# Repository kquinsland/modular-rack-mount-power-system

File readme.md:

# Modular Rack Power

This is a "side-quest" project on the way to building a small "mini rack" dedicated to hosting GH/A runners.

I'll do the CAD and standalone development here before integrating it into the larger project.
The goal is to have a modular system of a backplane and multiple carrier modules that can be swapped in and out to provide different power configurations as needed.
As long as the power supply can handle it, backplanes may share/daisy-chain the
input distribution needed by their carrier modules.

Hardware, firmware, and host tooling for a modular mini-rack power system.

## Boards

- `backplane`: STM32C092/CAN-FD backplane with six carrier slots, power
  distribution, aggregate current monitoring, fan control, and a status
  NeoPixel.
- `carrier`: Mates with one backplane slot and hosts an SW3538 USB-C PD module.

Every backplane and carrier is an independent STM32C092 CAN-FD node. There is no
I2C mux and no controller/proxy relationship between nodes. Earlier hardware and
firmware were research prototypes and are not compatibility targets.

## Layout

```text
firmware/
  Cargo.toml
  backplane/
  carrier/
  bootloader/
  crates/
  tools/
  xtask/
  docs/pdcan/
hardware/
  boards/
    backplane/
    carrier/
  libraries/
    symbols/
    footprints/
    3dmodels/
  mechanical/
docs/
scripts/
build/
releases/
```

`build/` is for generated local outputs. `releases/` is for fabrication packages that should be preserved exactly as sent to a board house.

See [`firmware/README.md`](firmware/README.md) for workspace commands and the
current hardware/firmware contract. Run `mise run firmware:check` from this
directory, or run Cargo commands from `firmware/`. The reviewed implementation
plan is kept in [`firmware/plan.md`](firmware/plan.md).

## Documentation site

The public-facing project documentation is maintained in [`site/`](site/) and
is intended for <https://mrps.karlquinsland.com/>. Run `mise run site:serve` for
local preview or `mise run site:build` for a production build. Create journal
entries with `mise run worklog:new -- "Concise Summary"` to create
`site/content/worklogs/YYYY/MM/DD - Concise Summary/index.md` with matching
front matter and an adjacent `_files/` directory for page resources.

## Misc

I can't believe that it's STILL such a pain in the ass to use LCSC to search for parts that are stocked by the SMT service.
https://yaqwsx.github.io/jlcparts/#/

Also super useful reference: https://www.tinkervault.com/usb-power-sources/dc-pd30-adapters
It's how I 'caught' that the `sw3538` based module I am using is non-standard 140W, later confirmed:

- https://en.eeworld.com.cn/Reference_Designs/detail/81702
- https://github.com/happyme531/h1_SW35xx/issues/13#issuecomment-4361605621

https://github.com/Shrike-Lab/HomeLab-PDU-V1/blob/main/ASSEMBLY/README.md#pcb-tray

Plan was to use APK43070 but they do not support MCU controlling it via i2c

https://meron33.hatenablog.com/entry/2026/02/07/112759

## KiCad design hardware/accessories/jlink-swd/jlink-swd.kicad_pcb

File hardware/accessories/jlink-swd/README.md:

# J-Link SWD adapter

This standalone 51.2 × 42 mm, two-layer board plugs directly into the SEGGER 20-pin ARM debug port. The keyed six-pin cable reaches backplane J10 or carrier J2. Both targets use the same contact assignments.

| Ref | Fit | Assembly |
| --- | --- | --- |
| J1 | Sullins SFH11-PBPC-D10-RA-BK ([LCSC C3319874](https://www.lcsc.com/product-detail/C3319874.html)) | Polarized 2×10 right-angle **female** socket, component side. Its mouth projects 7.74 mm past the PCB edge. |
| J2 | Leave empty | Central 2×10 through-hole tap. Every position connects to the same numbered position on J1. |
| J3 | 2×3 keyed vertical IDC **male** box header, 2.54 mm | Match the shroud opening to the footprint outline. Plug the TC2030-IDC-NL ribbon socket in here. |
| J4 | 2×2 straight male pin header, 2.54 mm | Pins 1 and 3 tap J-Link pin 19 (5 V where supported). Pins 2 and 4 are GND. |
| J5 | External 3.3 V input, 1×2 | Pin 1 is regulated 3.3 V, pin 2 is GND. |
| J6 | Source selector, 1×3 | Fit one shunt. Pins 1–2 select J-Link pin 1 (VTref), pins 2–3 select J5. |
| J7 | Target-current link, 1×2 | Pin 1 is the selected source, pin 2 is the target rail. Fit a shunt for normal adapter-powered operation. |
| J10 | Clone 3.3 V auxiliary tap, 2×2 | Pins 1 and 3 tap J-Link pin 2. Pins 2 and 4 are GND. |
| H1–H4 | 3.0 mm plated GND holes with 6.0 mm exposed pads | Hole centers form a 40.8 × 35.0 mm rectangle. Each pad connects to the top and bottom GND pours. Conductive mounting hardware touching a pad shares the target and J-Link ground. |

## Probe connections

| J3 / target pad | Signal | J1 / J2 |
| ---: | --- | --- |
| 1 | Target 3V3 | 1 through J6 (1–2) and J7 |
| 2 | SWDIO | 7 |
| 3 | Active-low reset | 15 |
| 4 | SWCLK | 9 |
| 5 | GND | 4, 6, 8, 10, 12 |
| 6 | Open | — |

## Power and current profiling

Change shunts with the probe and target unpowered. J4 and J10 each provide two power/GND pairs for leads. A shunt across either pair would short the supply. The odd-numbered column carries power and the even-numbered column is ground. Pin 1 has a square pad.

| Mode | J6 | J7 | Connection |
| --- | --- | --- | --- |
| Self-powered target with standard VTref sensing | 1–2 | Fit | Target 3.3 V reaches the probe’s pin 1 so it can sense the target logic level. |
| Probe with a verified supply on **pin 1** | 1–2 | Fit | Pin 1 can feed an otherwise unpowered target only when that probe explicitly supports it. |
| External regulated 3.3 V | 2–3 | Fit | Connect supply positive to J5.1 and return to J5.2. Probe pin 1 is isolated. |
| Measure current supplied by the adapter | Select the active supply | Replace shunt with ammeter | Meter positive to J7.1 (source), return to J7.2 (target). |

SEGGER specifies pin 1 as a target-voltage reference input. Selecting VTref with a standard probe and an unpowered target supplies no power. Conversely, external mode disconnects the probe’s VTref input, so a debugger that requires target-voltage sensing may refuse to attach in that mode. To debug an independently powered target using standard voltage sensing, use the first row.

The clone’s pin-2 output is available at J10 independently of J6. Verify the voltage and current capability of the particular probe before drawing power. To use that output as the target supply, patch J10.1 or J10.3 to J5.1, select EXT and fit J7. For a profiler with its own supply, feed J5 directly from the profiler. When the adapter powers the target, disconnect its normal power input. Grounds remain common throughout.

Reserved J-Link contacts 14, 16, 18, and 20 each have their own tap.

J2’s front silkscreen follows the SEGGER pin numbers. Odd positions are on the left and even positions on the right when the text is upright. R denotes a reserved position. P2 marks the optional clone supply and NC marks pin 17.

## Mating orientation

With J1's polarization bump up, looking into the **female mating face**, the upper row runs from SEGGER pin 1 at the left to pin 19 at the right. The lower row runs from pin 2 to pin 20. The upper contacts bend to the through-hole row farther from the board edge. The square J1 pad is VTref. Before powering a first assembly, verify continuity from that socket contact through J6 (1–2) and the fitted J7 link to J3 pin 1 and from the opposite end of the same row to both J4 pins 1 and 3.

See the [SEGGER 20-pin connector drawing](https://kb.segger.com/20-pin_J-Link_Connector), the [Sullins SFH11 mechanical drawing](https://sullinscorp.com/catalogs/147_PAGE119_.100_SFH11_SERIES_FEMALE_HDR_ST_RA.pdf), and the [TC2030-IDC-NL cable pin map, sheet 2](https://www.tag-connect.com/wp-content/uploads/bsk-pdf-manager/2019/12/TC2030-IDC-NL-Datasheet-Rev-B.pdf#page=2).

The project includes a [mechanical STEP model of J1](models/SFH11-PBPC-D10-RA-BK.step) with a keyed housing, mating openings, and 20 solder tails. It was drawn from the Sullins dimensions and the assembly outline for this part in the [TI reference design](https://www.ti.com/lit/zip/SWRC397). Internal spring contacts are omitted.

## Production export

The front silkscreen identifies revision 1.1. The KiCad editor displays `YY-MM-DD` and `UNRELEASED` as working-copy placeholders, as on the main boards. After committing the layout being fabricated, generate the fabrication files and purchasing BOM with KiCad 10 and the JLCPCB Fabrication Toolkit installed:

```sh
mise run production:jlink-swd
```

The default output directory is `hardware/accessories/jlink-swd/production/YY.MM.DD-<hash>/`. The directory name and silkscreen both use the commit’s UTC date and first 12 hex digits. To choose a different destination, run `mise run production:jlink-swd /path/to/output`.

Select bare-board fabrication and upload only `jlink-swd.zip`. All connector pads and drills are included for hand soldering. The separate `positions.csv` contains its column headings and zero placement rows. The export also writes the footprint inventory (`designators.csv`) and electrical-test netlist (`netlist.ipc`).

Use `bom.csv` for the hand-assembled components. Leave J2 empty and obtain two removable 2.54 mm jumper shunts for J6 and J7.

The task uses `/usr/bin/python3` by default. Set `KICAD_PYTHON` to another interpreter with the KiCad and wxPython bindings if needed.

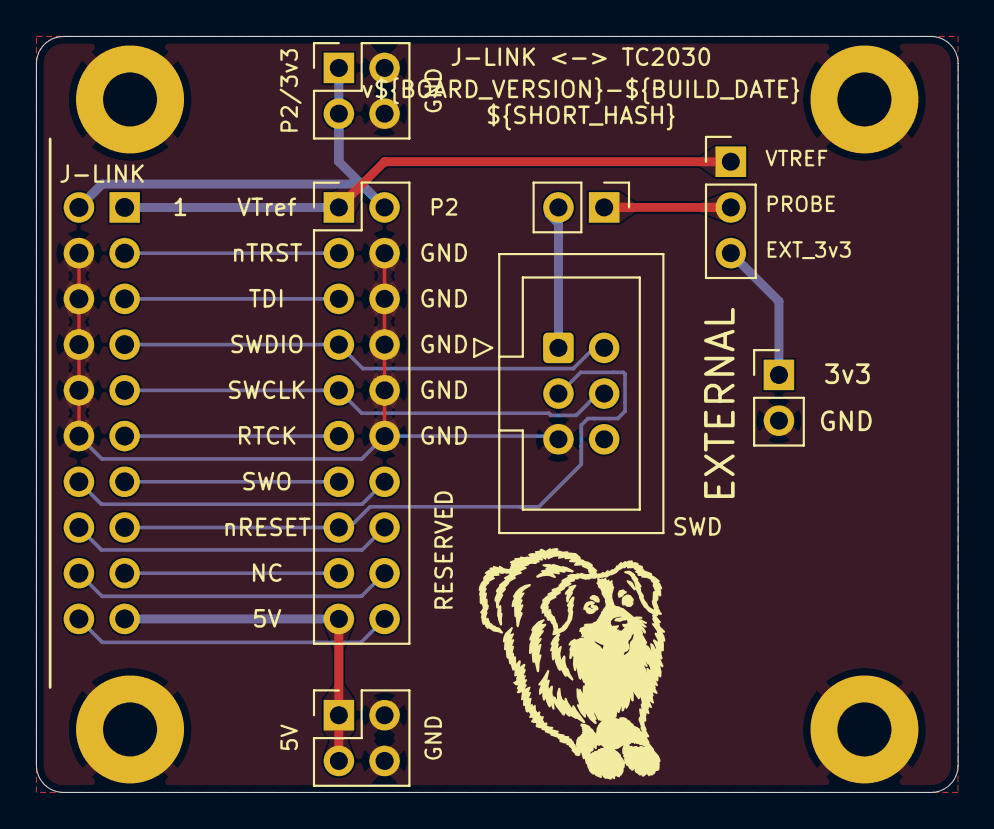
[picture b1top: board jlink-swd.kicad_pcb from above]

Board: 2 copper layers, 51.2 x 42.0 mm, 12 parts (0 on the bottom side), 19 nets.

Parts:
H1, H2, H3, H4: 3.0 mm; MountingHole_3mm_Pad
J1: SFH11-PBPC-D10-RA-BK
J2: 20-pin tap (DNP); PinHeader_2x10_P2.54mm_Vertical
J3: TC2030-IDC-NL; IDC-Header_2x03_P2.54mm_Vertical
J4: 5V / GND taps; PinHeader_2x02_P2.54mm_Vertical
J5: External 3.3V; PinHeader_1x02_P2.54mm_Vertical
J6: 3.3V source; PinHeader_1x03_P2.54mm_Vertical
J7: Target current; PinHeader_1x02_P2.54mm_Vertical
J10: Clone 3V3 / GND taps; PinHeader_2x02_P2.54mm_Vertical

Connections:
+3V3: J3.1, J7.2
+5V: J1.19, J2.19, J4.1, J4.3
/EXT_3V3: J5.1, J6.3
/P2: J1.2, J2.2, J10.1, J10.3
/P17: J1.17, J2.17
/PROBE_VTREF: J1.1, J2.1, J6.1
/RES14: J1.14, J2.14
/RES16: J1.16, J2.16
/RES18: J1.18, J2.18
/RES20: J1.20, J2.20
/RTCK: J1.11, J2.11
/SELECTED_3V3: J6.2, J7.1
/SWCLK: J1.9, J2.9, J3.4
/SWDIO: J1.7, J2.7, J3.2
/SWO: J1.13, J2.13
/TDI: J1.5, J2.5
/nRESET: J1.15, J2.15, J3.3
/nTRST: J1.3, J2.3
GND: H1.1, H2.1, H3.1, H4.1, J1.4, J1.6, J1.8, J1.10, J1.12, J2.4, J2.6, J2.8, J2.10, J2.12, J3.5, J4.2, J4.4, J5.2, J10.2, J10.4

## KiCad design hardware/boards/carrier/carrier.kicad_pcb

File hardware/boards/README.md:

# Boards

Each physical PCB gets its own KiCad project directory.

Current boards:

- `backplane`
- `carrier`

Both active boards use the same STM32C092GCU6 and direct CAN-FD architecture.
The backplane and carrier directories are the only product board definitions;
earlier research layouts are not compatibility targets. Some shared library
nicknames retain their original internal name so the finalized KiCad references
remain stable.

Future boards should follow the same pattern: `hardware/boards/<board-name>/<board-name>.kicad_pro`.

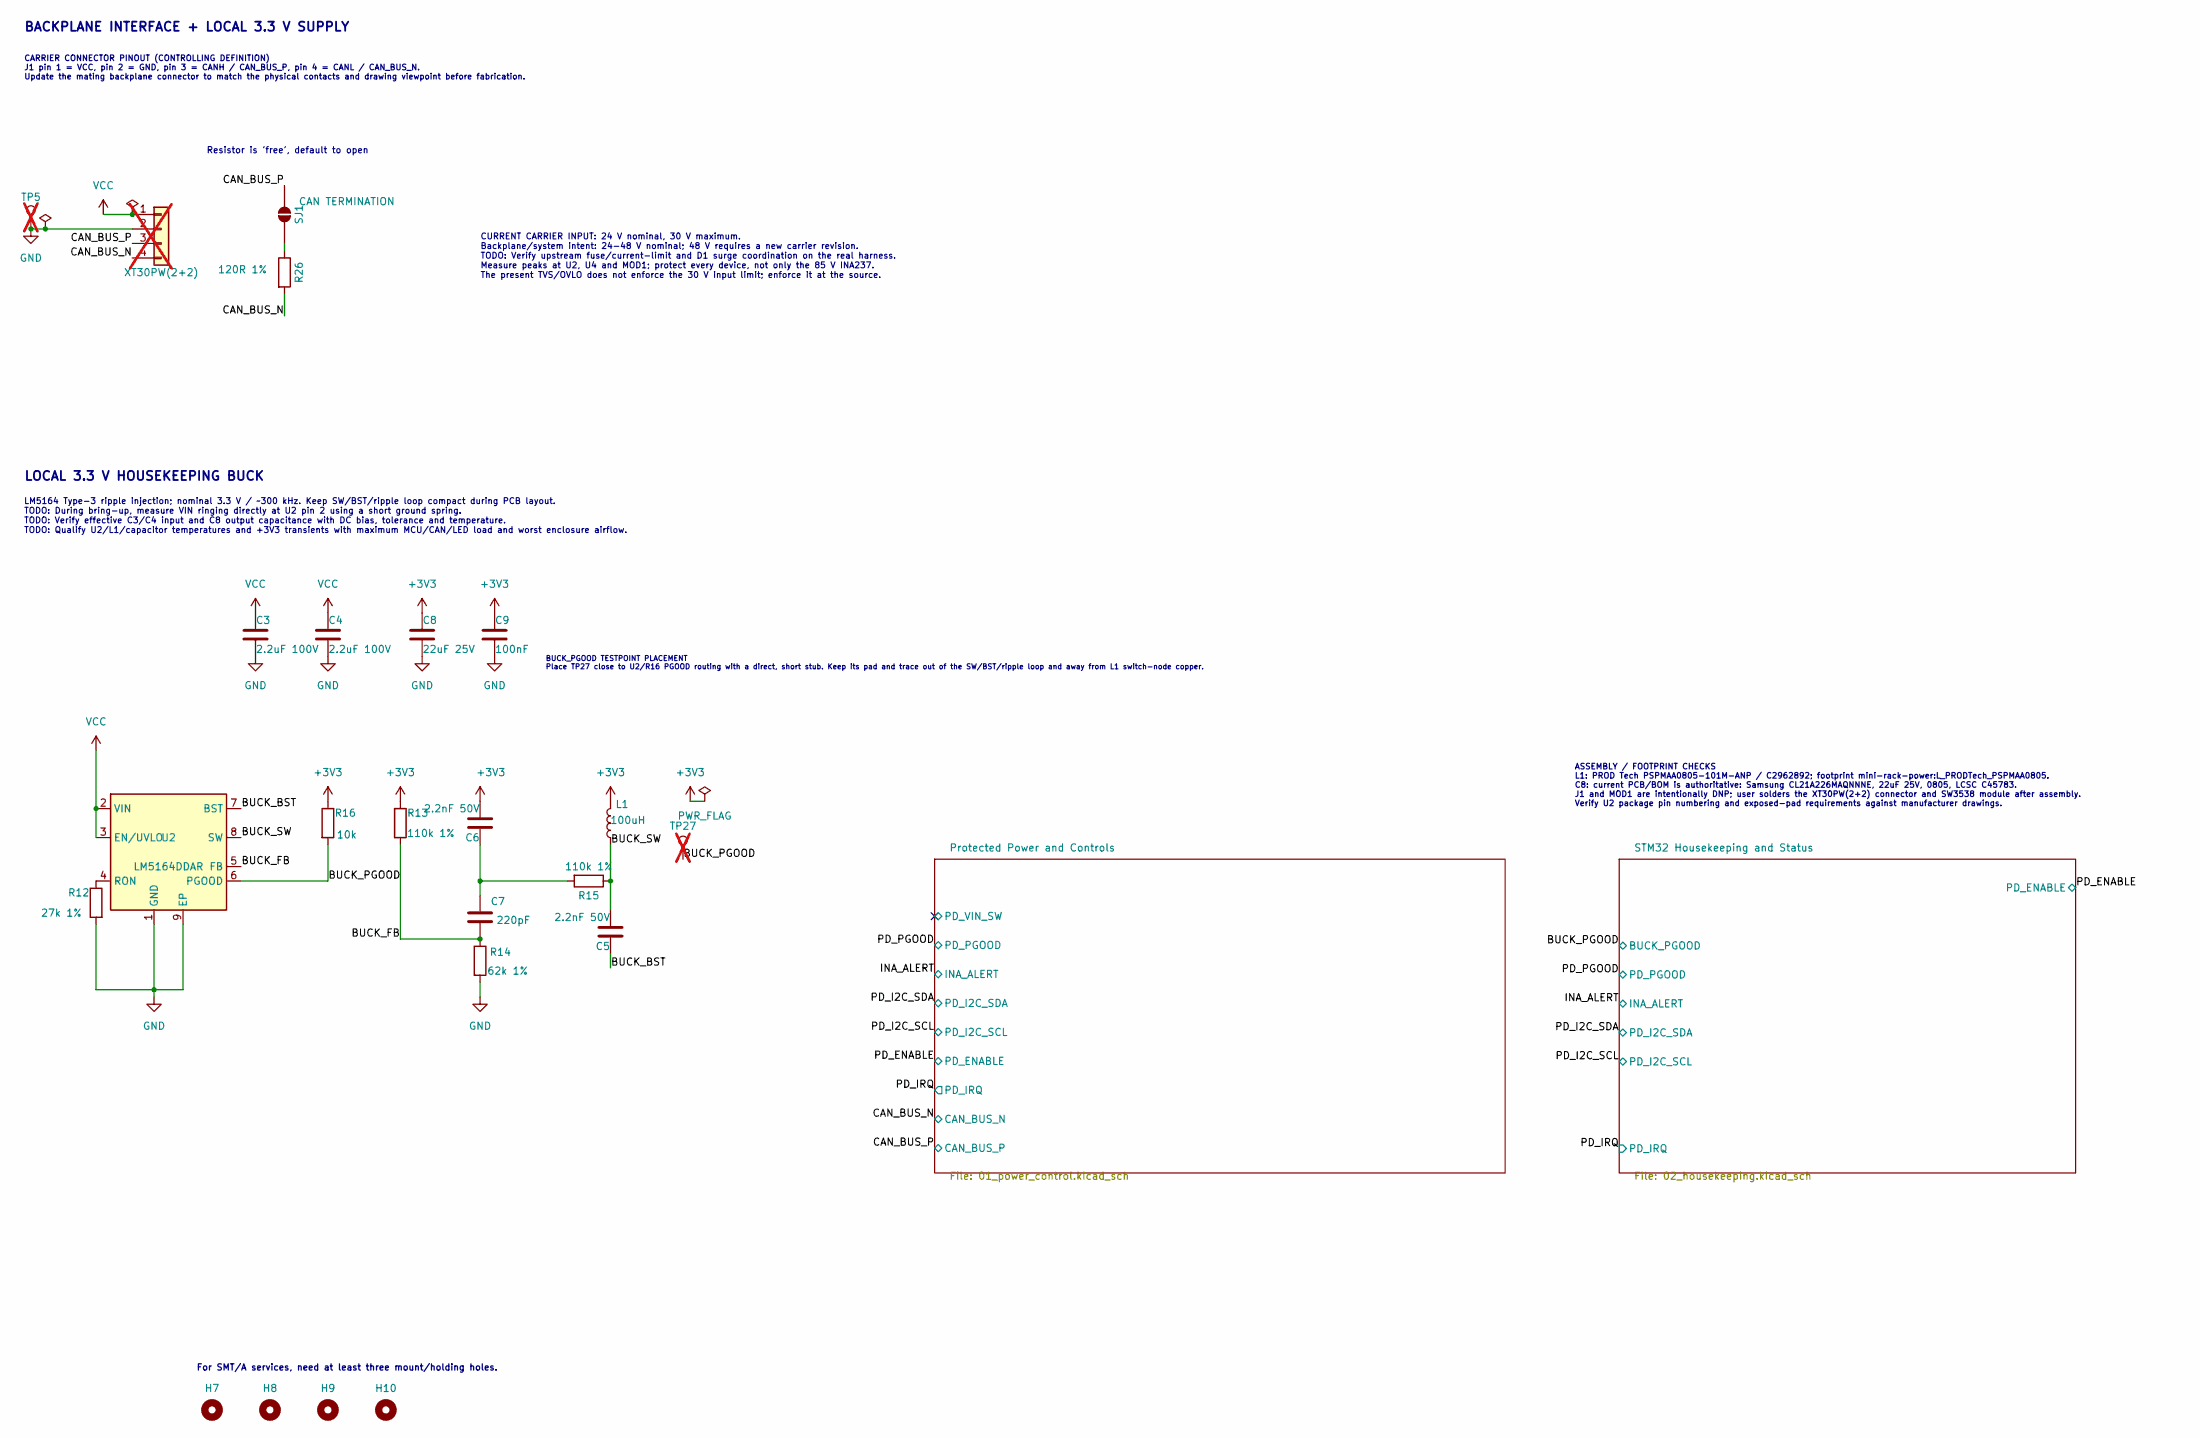
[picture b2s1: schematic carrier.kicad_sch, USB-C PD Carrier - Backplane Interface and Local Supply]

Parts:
C3, C4: 2.2uF 100V; C_1210_3225Metric; MPN CL32B225KCJSNNE; LCSC C55151
C5, C6: 2.2nF 50V; C_0603_1608Metric; MPN 0603B222K500NT; LCSC C1604
C7: 220pF; C_0603_1608Metric; MPN CC0603JRNPO9BN221; LCSC C106210
C8: 22uF 25V; C_0805_2012Metric; MPN CL21A226MAQNNNE; LCSC C45783
C9: 100nF; C_0603_1608Metric; MPN CC0603KRX7R9BB104; LCSC C14663
H7, H8, H9, H10: ToolingHole_1.152mm; MountingHole_JLCPCB_Tooling_1.152mm
J1: XT30PW(2+2); Amass_XT30PW_2plus2_M_RightAngle_THT; MPN XT30PW(2+2)-M.G.B; LCSC C19268030; not fitted
L1: 100uH; L_PRODTech_PSPMAA0805; MPN PSPMAA0805-101M-ANP; LCSC C2962892
R12: 27k 1%; R_0603_1608Metric; MPN 0603WAF2702T5E; LCSC C22967
R13, R15: 110k 1%; R_0603_1608Metric; MPN 0603WAF1103T5E; LCSC C25805
R14: 62k 1%; R_0603_1608Metric; MPN 0603WAF6202T5E; LCSC C23221
R16: 10k; R_0603_1608Metric; MPN 0603WAF1002T5E; LCSC C25804
R26: 120R 1%; R_0603_1608Metric; MPN 0603WAF1200T5E; LCSC C22787
SJ1: CAN TERMINATION; SolderJumper-2_P1.3mm_Open_Pad1.0x1.5mm; MPN PCB feature
TP5: GND; TestPoint_Pad_D1.0mm; not fitted
TP27: BUCK_PGOOD; TestPoint_Pad_D1.5mm; MPN PCB test point; not fitted
U2: LM5164DDAR; TI_SO-PowerPAD-8; MPN LM5164DDAR; LCSC C477928

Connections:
+3V3: C6.2, C8.1, C9.1, L1.2, R13.1, R16.1; also elsewhere on the board
/BUCK_BST: C5.1, U2.7 (BST)
/BUCK_FB: C7.2, R13.2, R14.1, U2.5 (FB)
/BUCK_PGOOD: R16.2, TP27.1 (1_1), U2.6 (PGOOD); also elsewhere on the board
/BUCK_SW: C5.2, L1.1, R15.1, U2.8 (SW)
/CAN_BUS_N: J1.4, R26.2; also elsewhere on the board
/CAN_BUS_P: J1.3, SJ1.1 (A); also elsewhere on the board
GND: C3.2, C4.2, C8.2, C9.2, J1.2, R12.2, R14.2, TP5.1 (1_1), U2.1 (GND), U2.9 (EP); also elsewhere on the board
unnamed: C6.1, C7.1, R15.2
unnamed: R26.1, SJ1.2 (B)
unnamed: R12.1, U2.4 (RON)
VCC: C3.1, C4.1, J1.1, U2.2 (VIN), U2.3 (EN/UVLO); also elsewhere on the board

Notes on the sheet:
CURRENT CARRIER INPUT: 24 V nominal, 30 V maximum. Backplane/system intent: 24-48 V nominal; 48 V requires a new carrier revision. TODO: Verify upstream fuse/current-limit and D1 surge coordination on the real harness. Measure peaks at U2, U4 and MOD1; protect every device, not only the 85 V INA237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
LOCAL 3.3 V HOUSEKEEPING BUCK
ASSEMBLY / FOOTPRINT CHECKS L1: PROD Tech PSPMAA0805-101M-ANP / C2962892; footprint mini-rack-power:L_PRODTech_PSPMAA0805. C8: current PCB/BOM is authoritative: Samsung CL21A226MAQNNNE, 22uF 25V, 0805, LCSC C45783. J1 and MOD1 are intentionally DNP; user solders the XT30PW(2+2) connector and SW3538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
Resistor is 'free', default to open
LM5164 Type-3 ripple injection; nominal 3.3 V / ~300 kHz. Keep SW/BST/ripple loop compact during PCB layout. TODO: During bring-up, measure VIN ringing directly at U2 pin 2 using a short ground spring. TODO: Verify effective C3/C4 input and C8 output capacitance with DC bias, tolerance and temperat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
BUCK_PGOOD TESTPOINT PLACEMENT Place TP27 close to U2/R16 PGOOD routing with a direct, short stub. Keep its pad and trace out of the SW/BST/ripple loop and away from L1 switch-node copper.
For SMT/A services, need at least three mount/holding holes.
CARRIER CONNECTOR PINOUT (CONTROLLING DEFINITION) J1 pin 1 = VCC, pin 2 = GND, pin 3 = CANH / CAN_BUS_P, pin 4 = CANL / CAN_BUS_N. Update the mating backplane connector to match the physical contacts and drawing viewpoint before fabrication.
BACKPLANE INTERFACE + LOCAL 3.3 V SUPPLY

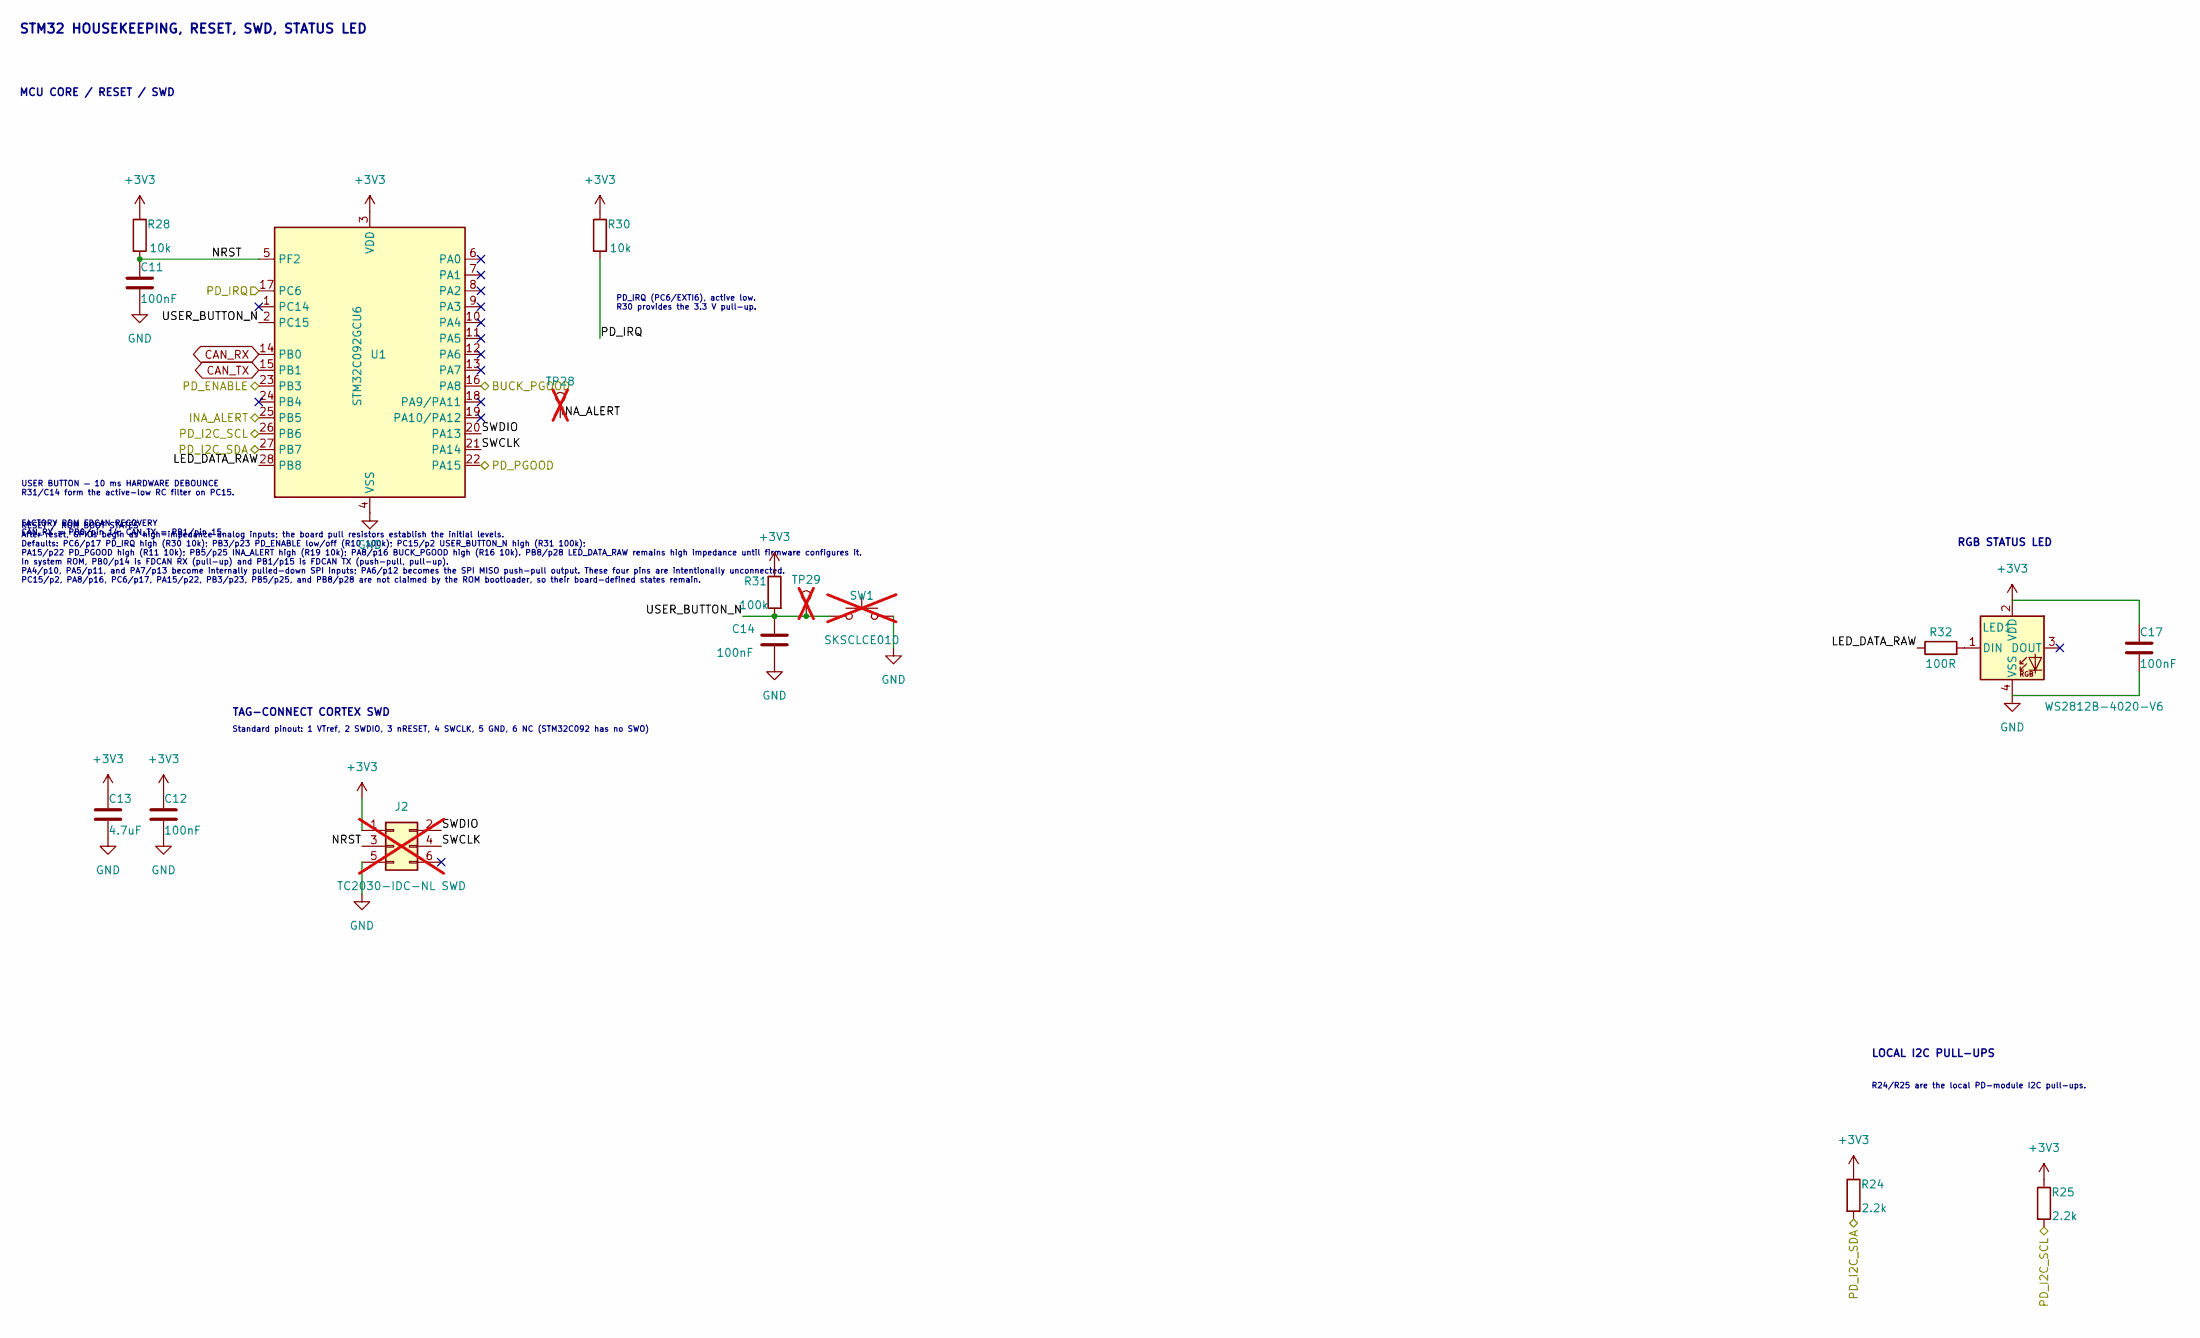
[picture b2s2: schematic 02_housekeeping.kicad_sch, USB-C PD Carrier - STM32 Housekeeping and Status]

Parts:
C11, C12, C14, C17: 100nF; C_0603_1608Metric; MPN CC0603KRX7R9BB104; LCSC C14663
C13: 4.7uF; C_0603_1608Metric; MPN CL10A475KO8NNNC; LCSC C19666
J2: TC2030-IDC-NL SWD; Tag-Connect_TC2030-IDC-NL_2x03_P1.27mm_Vertical; MPN TC2030-IDC-NL; not fitted
LED1: WS2812B-4020-V6; LED_Worldsemi_WS2812B-4020-V6_SideView; MPN WS2812B-4020-V6; LCSC C52941387
R24, R25: 2.2k; R_0603_1608Metric; MPN 0603WAF2201T5E; LCSC C4190
R28, R30: 10k; R_0603_1608Metric; MPN 0603WAF1002T5E; LCSC C25804
R31: 100k; R_0603_1608Metric; MPN 0603WAF1003T5E; LCSC C25803
R32: 100R; R_0603_1608Metric; MPN 0603WAF1000T5E; LCSC C22775
SW1: SKSCLCE010; SW_ALPS_SKSCLCE010_SidePush; MPN SKSCLCE010; LCSC C139799; not fitted
TP28: INA_ALERT; TestPoint_Pad_D1.5mm; MPN PCB test point; not fitted
TP29: USER_BUTTON_N; TestPoint_Pad_D1.5mm; MPN PCB test point; not fitted
U1: STM32C092GCU6; QFN-28_4x4mm_P0.5mm; MPN STM32C092GCU6; LCSC C44847705

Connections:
+3V3: C12.1, C13.1, C17.1, J2.1, LED1.2 (VDD), R24.1, R25.1, R28.1, R30.1, R31.1, U1.3 (VDD); also elsewhere on the board
/BUCK_PGOOD: U1.16 (PA8); also elsewhere on the board
/INA_ALERT: TP28.1 (1_1), U1.25 (PB5); also elsewhere on the board
/PD_ENABLE: U1.23 (PB3); also elsewhere on the board
/PD_I2C_SCL: R25.2, U1.26 (PB6); also elsewhere on the board
/PD_I2C_SDA: R24.2, U1.27 (PB7); also elsewhere on the board
/PD_IRQ: R30.2, U1.17 (PC6); also elsewhere on the board
/PD_PGOOD: U1.22 (PA15); also elsewhere on the board
/STM32 Housekeeping and Status/LED_DATA_RAW: R32.1, U1.28 (PB8)
/STM32 Housekeeping and Status/NRST: C11.1, J2.3, R28.2, U1.5 (PF2)
/STM32 Housekeeping and Status/SWCLK: J2.4, U1.21 (PA14)
/STM32 Housekeeping and Status/SWDIO: J2.2, U1.20 (PA13)
/STM32 Housekeeping and Status/USER_BUTTON_N: C14.1, R31.2, SW1.2, TP29.1 (1_1), U1.2 (PC15)
CAN_RX: U1.14 (PB0); also elsewhere on the board
CAN_TX: U1.15 (PB1); also elsewhere on the board
GND: C11.2, C12.2, C13.2, C14.2, C17.2, J2.5, LED1.4 (VSS), SW1.1, U1.4 (VSS); also elsewhere on the board
unnamed: LED1.1 (DIN), R32.2

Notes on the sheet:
Standard pinout: 1 VTref, 2 SWDIO, 3 nRESET, 4 SWCLK, 5 GND, 6 NC (STM32C092 has no SWO)
FACTORY ROM FDCAN RECOVERY CAN_RX = PB0/pin 14; CAN_TX = PB1/pin 15.
LOCAL I2C PULL-UPS
USER BUTTON — 10 ms HARDWARE DEBOUNCE R31/C14 form the active-low RC filter on PC15.
R24/R25 are the local PD-module I2C pull-ups.
TAG-CONNECT CORTEX SWD
MCU CORE / RESET / SWD
STM32 HOUSEKEEPING, RESET, SWD, STATUS LED
PD_IRQ (PC6/EXTI6), active low. R30 provides the 3.3 V pull-up.
RESET / ROM BOOT STATES After reset, GPIOs begin as high-impedance analog inputs; the board pull resistors establish the initial levels. Defaults: PC6/p17 PD_IRQ high (R30 10k); PB3/p23 PD_ENABLE low/off (R10 100k); PC15/p2 USER_BUTTON_N high (R31 100k); PA15/p22 PD_PGOOD high (R11 10k); PB5/p25 IN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
RGB STATUS LED

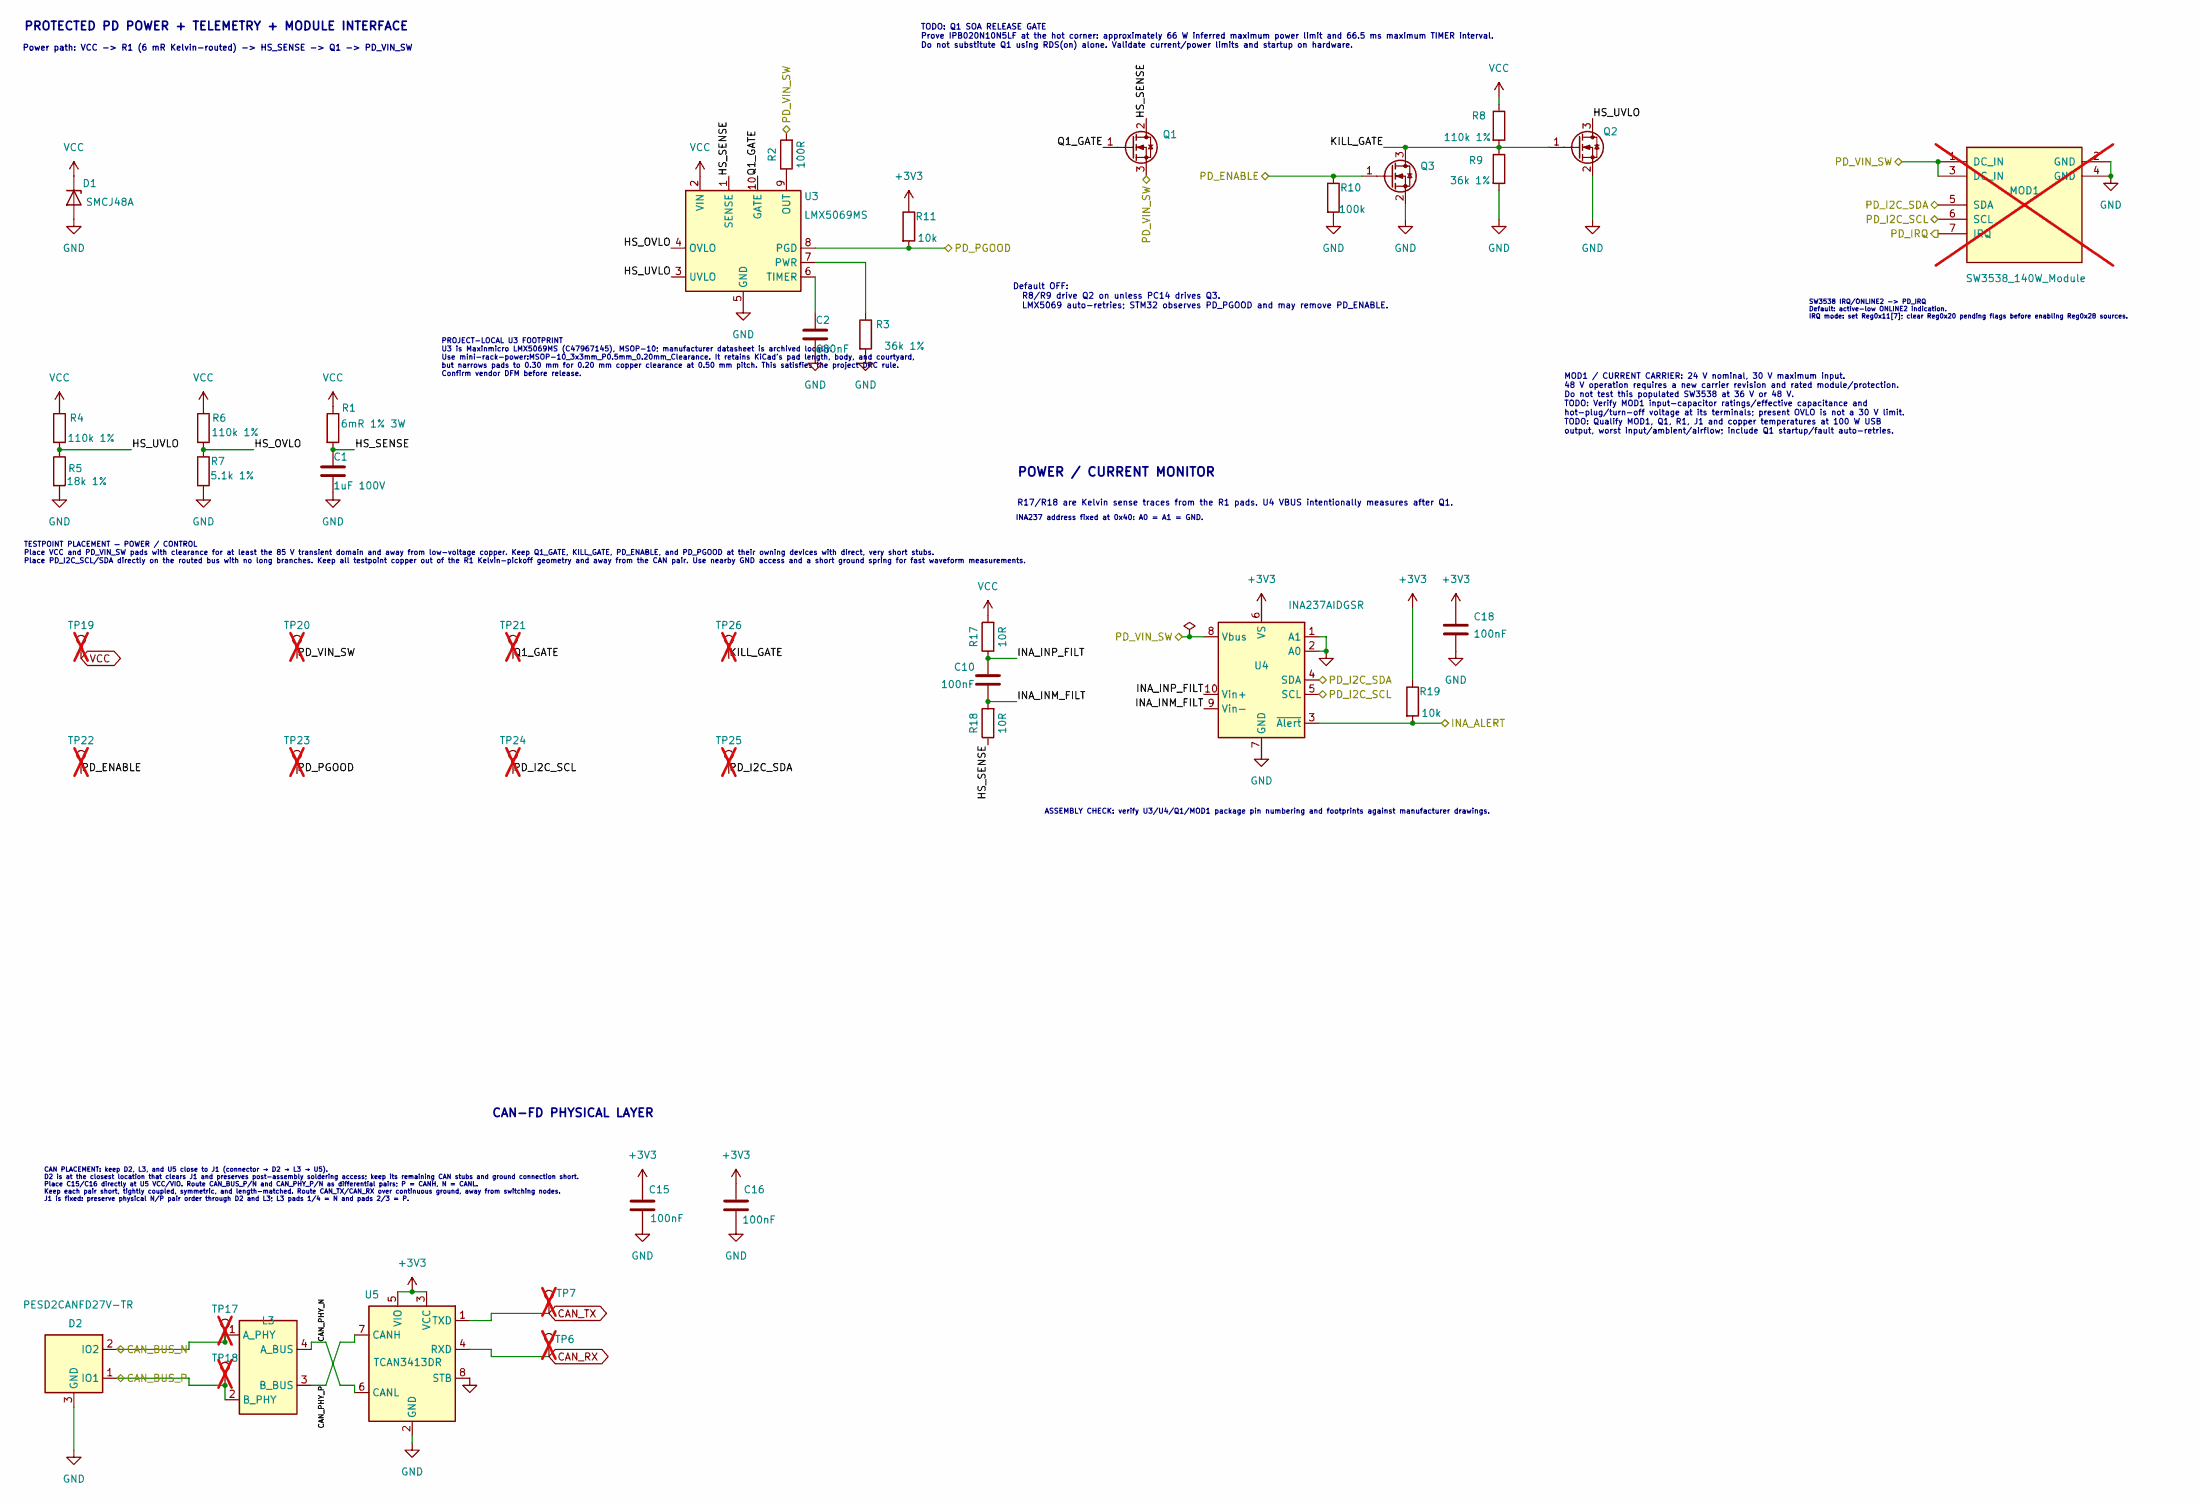
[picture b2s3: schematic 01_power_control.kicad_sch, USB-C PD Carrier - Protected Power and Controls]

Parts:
C1: 1uF 100V; C_1206_3216Metric; MPN CL31B105KCHNNNE; LCSC C13832
C2: 680nF; C_0603_1608Metric; MPN 0603B684K160NT; LCSC C24797
C10, C15, C16, C18: 100nF; C_0603_1608Metric; MPN CC0603KRX7R9BB104; LCSC C14663
D1: SMCJ48A; D_SMC_Silk0.15mm; MPN SMCJ48A; LCSC C19077611
D2: PESD2CANFD27V-TR; SOT-23; MPN PESD2CANFD27V-TR; LCSC C552488
L3: ACT1210D-101-2P-TL00; L_CommonModeChoke_TDK_ACT1210D; MPN ACT1210D-101-2P-TL00; LCSC C3039743
MOD1: SW3538_140W_Module; not fitted
Q1: IPB020N10N5LF; TO-263-3_TabPin2; MPN IPB020N10N5LF; LCSC C536484
Q2, Q3: 2N7002; SOT-23; MPN 2N7002; LCSC C8545
R1: 6mR 1% 3W; R_2512_6332Metric; MPN HoLLR2512-3W-6mR-1%; LCSC C2985709
R2: 100R; R_0603_1608Metric; MPN 0603WAF1000T5E; LCSC C22775
R3, R9: 36k 1%; R_0603_1608Metric; MPN 0603WAF3602T5E; LCSC C23147
R4, R6, R8: 110k 1%; R_0603_1608Metric; MPN 0603WAF1103T5E; LCSC C25805
R5: 18k 1%; R_0603_1608Metric; MPN 0603WAF1802T5E; LCSC C25810
R7: 5.1k 1%; R_0603_1608Metric; MPN 0603WAF5101T5E; LCSC C23186
R10: 100k; R_0603_1608Metric; MPN 0603WAF1003T5E; LCSC C25803
R11, R19: 10k; R_0603_1608Metric; MPN 0603WAF1002T5E; LCSC C25804
R17, R18: 10R; R_0603_1608Metric; MPN 0603WAF100JT5E; LCSC C22859
TP6: CAN_RX; TestPoint_Pad_D1.5mm; MPN PCB test point; not fitted
TP7: CAN_TX; TestPoint_Pad_D1.5mm; MPN PCB test point; not fitted
TP17: CAN_BUS_N; TestPoint_Pad_D1.5mm; MPN PCB test point; not fitted
TP18: CAN_BUS_P; TestPoint_Pad_D1.5mm; MPN PCB test point; not fitted
TP19: VCC; TestPoint_Pad_D1.5mm; MPN PCB test point; not fitted
TP20: PD_VIN_SW; TestPoint_Pad_D1.5mm; MPN PCB test point; not fitted
TP21: Q1_GATE; TestPoint_Pad_D1.5mm; MPN PCB test point; not fitted
TP22: PD_ENABLE; TestPoint_Pad_D1.5mm; MPN PCB test point; not fitted
TP23: PD_PGOOD; TestPoint_Pad_D1.5mm; MPN PCB test point; not fitted
TP24: PD_I2C_SCL; TestPoint_Pad_D1.5mm; MPN PCB test point; not fitted
TP25: PD_I2C_SDA; TestPoint_Pad_D1.5mm; MPN PCB test point; not fitted
TP26: KILL_GATE; TestPoint_Pad_D1.5mm; MPN PCB test point; not fitted
U3: LMX5069MS; MSOP-10_3x3mm_P0.5mm_0.20mm_Clearance; MPN LMX5069MS; LCSC C47967145
U4: INA237AIDGSR; TSSOP-10_3x3mm_P0.5mm; MPN INA237AIDGSR; LCSC C2864837
U5: TCAN3413DR; SOIC-8_3.9x4.9mm_P1.27mm; MPN TCAN3413DR; LCSC C22433320

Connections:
+3V3: C15.1, C16.1, C18.1, R11.1, R19.1, U4.6 (VS), U5.3 (VCC), U5.5 (VIO); also elsewhere on the board
/CAN_BUS_N: D2.2 (IO2), L3.1 (A_PHY), TP17.1 (1_1); also elsewhere on the board
/CAN_BUS_P: D2.1 (IO1), L3.2 (B_PHY), TP18.1 (1_1); also elsewhere on the board
/INA_ALERT: R19.2, U4.3 (~Alert); also elsewhere on the board
/PD_ENABLE: Q3.1 (G), R10.1, TP22.1 (1_1); also elsewhere on the board
/PD_I2C_SCL: MOD1.6 (SCL), TP24.1 (1_1), U4.5 (SCL); also elsewhere on the board
/PD_I2C_SDA: MOD1.5 (SDA), TP25.1 (1_1), U4.4 (SDA); also elsewhere on the board
/PD_IRQ: MOD1.7 (IRQ); also elsewhere on the board
/PD_PGOOD: R11.2, TP23.1 (1_1), U3.8 (PGD); also elsewhere on the board
/Protected Power and Controls/CAN_PHY_N: L3.4 (A_BUS), U5.6 (CANL)
/Protected Power and Controls/CAN_PHY_P: L3.3 (B_BUS), U5.7 (CANH)
/Protected Power and Controls/HS_OVLO: R6.2, R7.1, U3.4 (OVLO)
/Protected Power and Controls/HS_SENSE: C1.1, Q1.2 (D), R1.2, R18.1, U3.1 (SENSE)
/Protected Power and Controls/HS_UVLO: Q2.3 (D), R4.2, R5.1, U3.3 (UVLO)
/Protected Power and Controls/INA_INM_FILT: C10.2, R18.2, U4.9 (Vin-)
/Protected Power and Controls/INA_INP_FILT: C10.1, R17.1, U4.10 (Vin+)
/Protected Power and Controls/KILL_GATE: Q2.1 (G), Q3.3 (D), R8.2, R9.1, TP26.1 (1_1)
/Protected Power and Controls/PD_VIN_SW: MOD1.1 (DC_IN), MOD1.3 (DC_IN), Q1.3 (S), R2.2, TP20.1 (1_1), U4.8 (Vbus)
/Protected Power and Controls/Q1_GATE: Q1.1 (G), TP21.1 (1_1), U3.10 (GATE)
CAN_RX: TP6.1 (1_1), U5.4 (RXD); also elsewhere on the board
CAN_TX: TP7.1 (1_1), U5.1 (TXD); also elsewhere on the board
GND: C1.2, C2.2, C15.2, C16.2, C18.2, D1.2 (A), D2.3 (GND), MOD1.2 (GND), MOD1.4 (GND), Q2.2 (S), Q3.2 (S), R3.2, R5.2, R7.2, R9.2, R10.2, U3.5 (GND), U4.1 (A1), U4.2 (A0), U4.7 (GND), U5.2 (GND), U5.8 (STB); also elsewhere on the board
unnamed: R2.1, U3.9 (OUT)
unnamed: R3.1, U3.7 (PWR)
unnamed: C2.1, U3.6 (TIMER)
VCC: D1.1 (K), R1.1, R4.1, R6.1, R8.1, R17.2, TP19.1 (1_1), U3.2 (VIN); also elsewhere on the board

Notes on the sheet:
MOD1 / CURRENT CARRIER: 24 V nominal, 30 V maximum input. 48 V operation requires a new carrier revision and rated module/protection. Do not test this populated SW3538 at 36 V or 48 V. TODO: Verify MOD1 input-capacitor ratings/effective capacitance and hot-plug/turn-off voltage at its terminals; pr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
PROTECTED PD POWER + TELEMETRY + MODULE INTERFACE
INA237 address fixed at 0x40: A0 = A1 = GND.
TODO: Q1 SOA RELEASE GATE Prove IPB020N10N5LF at the hot corner: approximately 66 W inferred maximum power limit and 66.5 ms maximum TIMER interval. Do not substitute Q1 using RDS(on) alone. Validate current/power limits and startup on hardware.
R17/R18 are Kelvin sense traces from the R1 pads. U4 VBUS intentionally measures after Q1.
TESTPOINT PLACEMENT — POWER / CONTROL Place VCC and PD_VIN_SW pads with clearance for at least the 85 V transient domain and away from low-voltage copper. Keep Q1_GATE, KILL_GATE, PD_ENABLE, and PD_PGOOD at their owning devices with direct, very short stubs. Place PD_I2C_SCL/SDA directly on the rou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
PROJECT-LOCAL U3 FOOTPRINT U3 is Maxinmicro LMX5069MS (C47967145), MSOP-10; manufacturer datasheet is archived locally. Use mini-rack-power:MSOP-10_3x3mm_P0.5mm_0.20mm_Clearance. It retains KiCad's pad length, body, and courtyard, but narrows pads to 0.30 mm for 0.20 mm copper clearance at 0.50 mm 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
Default OFF: R8/R9 drive Q2 on unless PC14 drives Q3. LMX5069 auto-retries; STM32 observes PD_PGOOD and may remove PD_ENABLE.
CAN-FD PHYSICAL LAYER
CAN PLACEMENT: keep D2, L3, and U5 close to J1 (connector → D2 → L3 → U5). D2 is at the closest location that clears J1 and preserves post-assembly soldering access; keep its remaining CAN stubs and ground connection short. Place C15/C16 directly at U5 VCC/VIO. Route CAN_BUS_P/N and CAN_PHY_P/N as 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
SW3538 IRQ/ONLINE2 -> PD_IRQ Default: active-low ONLINE2 indication. IRQ mode: set Reg0x11[7]; clear Reg0x20 pending flags before enabling Reg0x28 sources.
ASSEMBLY CHECK: verify U3/U4/Q1/MOD1 package pin numbering and footprints against manufacturer drawings.
Power path: VCC -> R1 (6 mR Kelvin-routed) -> HS_SENSE -> Q1 -> PD_VIN_SW
POWER / CURRENT MONITOR

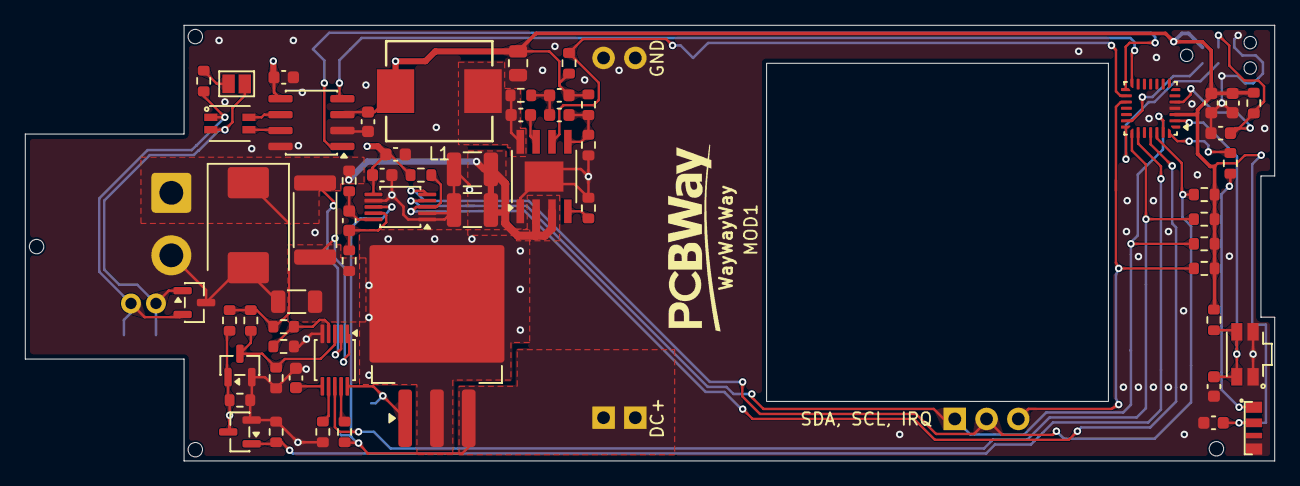
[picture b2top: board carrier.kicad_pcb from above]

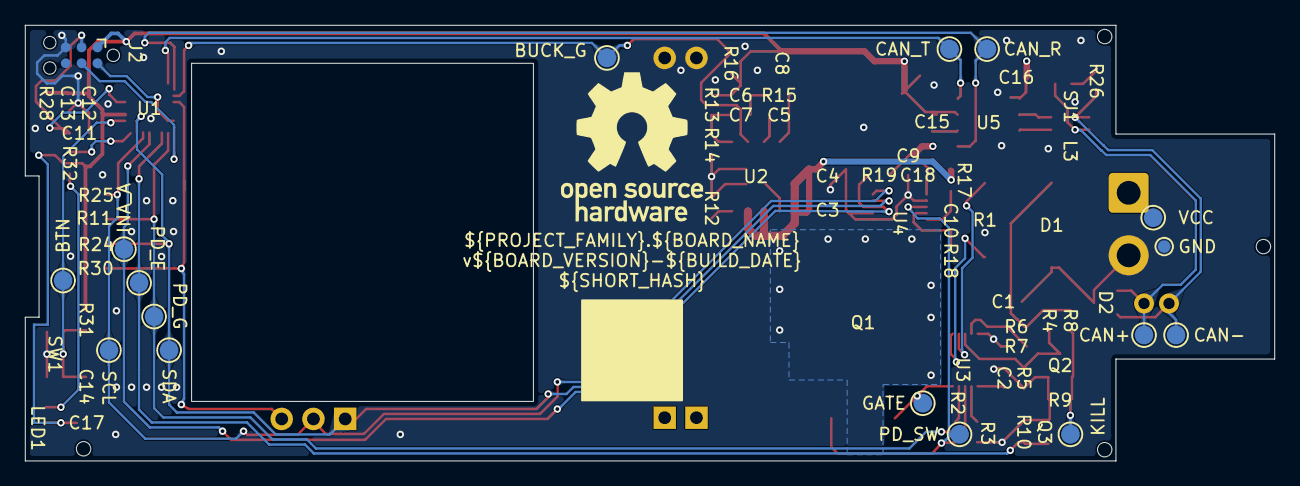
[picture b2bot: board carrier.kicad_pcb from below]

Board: 4 copper layers, 100.0 x 34.9 mm, 83 parts (17 on the bottom side), 39 nets.

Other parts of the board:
LOGO_PCBWAY: PCBWay_Logo_15mm

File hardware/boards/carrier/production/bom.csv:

Designator,Footprint,Quantity,Value,LCSC Part #
C1,C_1206_3216Metric,1,1uF 100V,C13832
C2,C_0603_1608Metric,1,680nF,C24797
"C3, C4",C_1210_3225Metric,2,2.2uF 100V,C55151
"C5, C6",C_0603_1608Metric,2,2.2nF 50V,C1604
C7,C_0603_1608Metric,1,220pF,C106210
C8,C_0805_2012Metric,1,22uF 25V,C45783
"C9, C10, C11, C12, C14, C15, C16, C17, C18",C_0603_1608Metric,9,100nF,C14663
C13,C_0603_1608Metric,1,4.7uF,C19666
D1,D_SMC_Silk0.15mm,1,SMCJ48A,C19077611
D2,SOT-23,1,PESD2CANFD27V-TR,C552488
L1,L_PRODTech_PSPMAA0805,1,100uH,C2962892
L3,L_CommonModeChoke_TDK_ACT1210D,1,ACT1210D-101-2P-TL00,C3039743
LED1,LED_Worldsemi_WS2812B-4020-V6_SideView,1,WS2812B-4020-V6,C52941387
Q1,TO-263-3_TabPin2,1,IPB020N10N5LF,C536484
"Q2, Q3",SOT-23,2,2N7002,C8545
R1,R_2512_6332Metric,1,6mR 1% 3W,C2985709
"R2, R32",R_0603_1608Metric,2,100R,C22775
"R3, R9",R_0603_1608Metric,2,36k 1%,C23147
"R4, R6, R8, R13, R15",R_0603_1608Metric,5,110k 1%,C25805
R5,R_0603_1608Metric,1,18k 1%,C25810
R7,R_0603_1608Metric,1,5.1k 1%,C23186
"R10, R31",R_0603_1608Metric,2,100k,C25803
"R11, R16, R19, R28, R30",R_0603_1608Metric,5,10k,C25804
R12,R_0603_1608Metric,1,27k 1%,C22967
R14,R_0603_1608Metric,1,62k 1%,C23221
"R17, R18",R_0603_1608Metric,2,10R,C22859
"R24, R25",R_0603_1608Metric,2,2.2k,C4190
R26,R_0603_1608Metric,1,120R 1%,C22787
U1,QFN-28_4x4mm_P0.5mm,1,STM32C092GCU6,C44847705
U2,TI_SO-PowerPAD-8,1,LM5164DDAR,C477928
U3,MSOP-10_3x3mm_P0.5mm_0.20mm_Clearance,1,LMX5069MS,C47967145
U4,TSSOP-10_3x3mm_P0.5mm,1,INA237AIDGSR,C2864837
U5,SOIC-8_3.9x4.9mm_P1.27mm,1,TCAN3413DR,C22433320
